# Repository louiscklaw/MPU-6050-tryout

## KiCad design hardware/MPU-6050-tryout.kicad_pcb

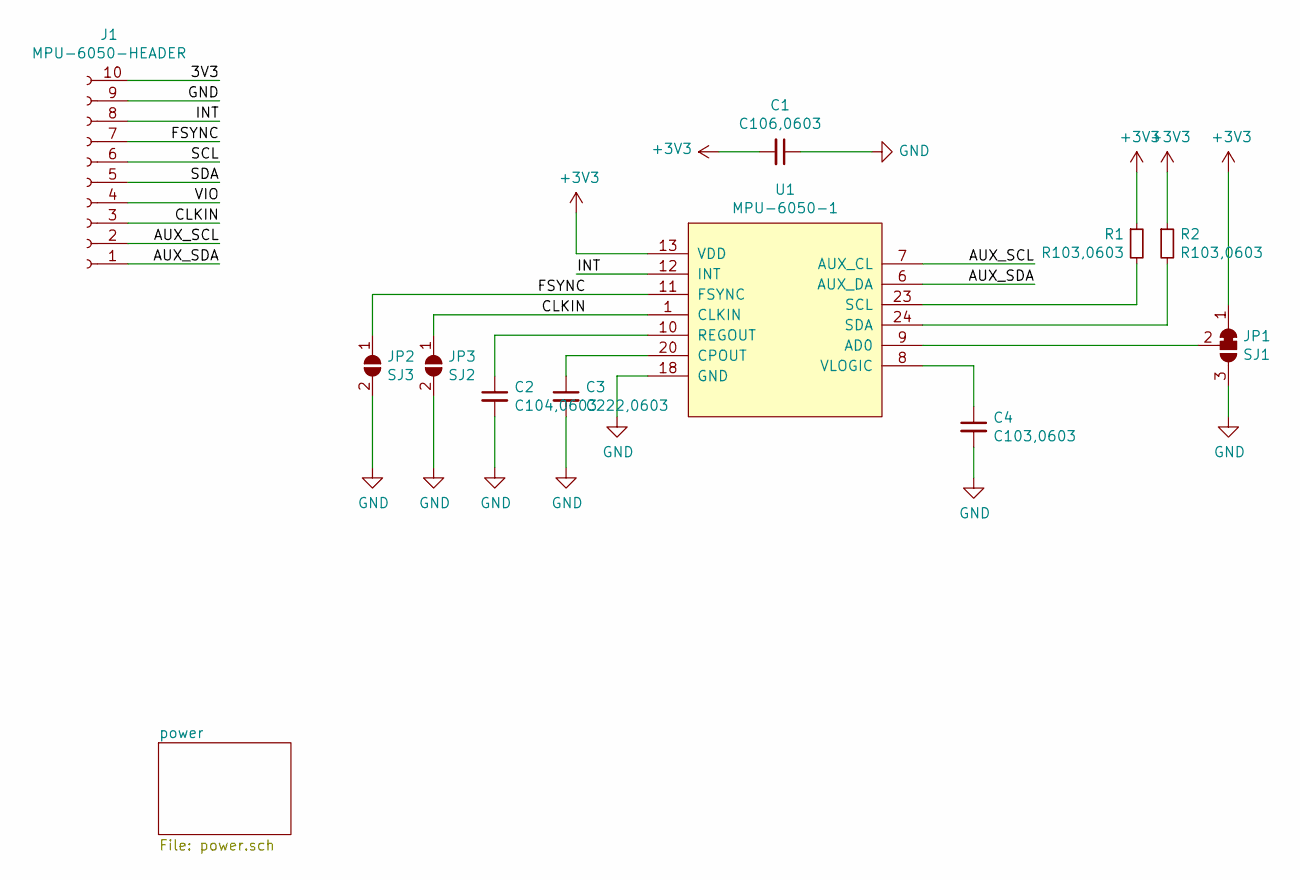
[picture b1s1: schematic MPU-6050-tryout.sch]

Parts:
C1: C106,0603; C_0603_1608Metric_Pad1.05x0.95mm_HandSolder
C2: C104,0603; C_0603_1608Metric_Pad1.05x0.95mm_HandSolder
C3: C222,0603; C_0603_1608Metric_Pad1.05x0.95mm_HandSolder
C4: C103,0603; C_0603_1608Metric_Pad1.05x0.95mm_HandSolder
J1: MPU-6050-HEADER; PinHeader_1x10_P1.27mm_Vertical
JP1: SJ1; SolderJumper-3_P1.3mm_Bridged2Bar12_Pad1.0x1.5mm
JP2: SJ3; SolderJumper-2_P1.3mm_Open_RoundedPad1.0x1.5mm
JP3: SJ2; SolderJumper-2_P1.3mm_Open_RoundedPad1.0x1.5mm
R1, R2: R103,0603; R_0603_1608Metric_Pad1.05x0.95mm_HandSolder
U1: MPU-6050-1; MPU-6050-QFN24

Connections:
+3V3: C1.2, JP1.1 (A), R1.1, R2.1, U1.13 (VDD); also elsewhere on the board
/3V3: J1.10
/AUX_SCL: J1.2, U1.7 (AUX_CL)
/AUX_SDA: J1.1, U1.6 (AUX_DA)
/CLKIN: J1.3, JP3.1 (A), U1.1 (CLKIN)
/FSYNC: J1.7, JP2.1 (A), U1.11 (FSYNC)
/INT: J1.8, U1.12 (INT)
/SCL: J1.6
/SDA: J1.5
/VIO: J1.4
GND: C1.1, C2.2, C3.2, C4.2, J1.9, JP1.3 (B), JP2.2 (B), JP3.2 (B), U1.18 (GND); also elsewhere on the board
unnamed: C2.1, U1.10 (REGOUT)
unnamed: C3.1, U1.20 (CPOUT)
unnamed: C4.1, U1.8 (VLOGIC)
unnamed: JP1.2 (C), U1.9 (AD0)
unnamed: R1.2, U1.23 (SCL)
unnamed: R2.2, U1.24 (SDA)

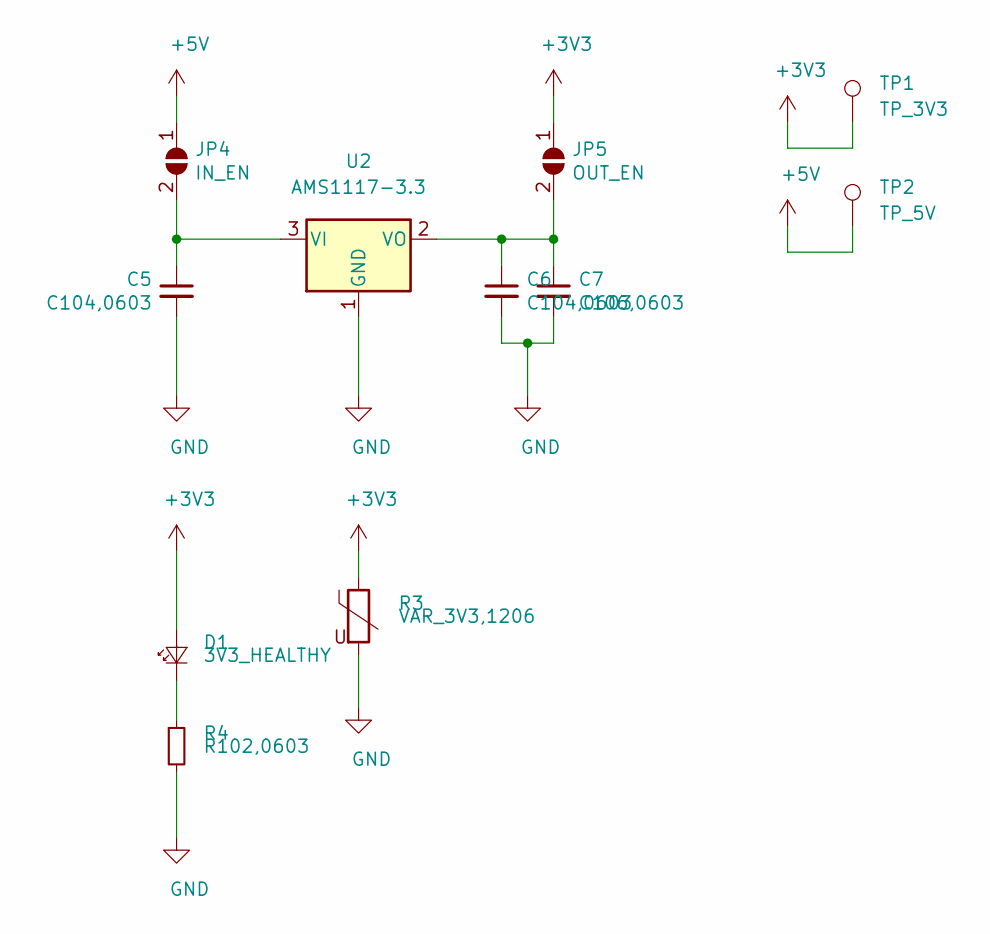
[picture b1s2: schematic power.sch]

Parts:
C5, C6: C104,0603; C_0603_1608Metric_Pad1.05x0.95mm_HandSolder
C7: C106,0603; C_0603_1608Metric_Pad1.05x0.95mm_HandSolder
D1: 3V3_HEALTHY; LED_0603_1608Metric_Pad1.05x0.95mm_HandSolder
JP4: IN_EN; SolderJumper-2_P1.3mm_Open_RoundedPad1.0x1.5mm
JP5: OUT_EN; SolderJumper-2_P1.3mm_Open_RoundedPad1.0x1.5mm
R3: VAR_3V3,1206; VAR_1206
R4: R102,0603; R_0603_1608Metric_Pad1.05x0.95mm_HandSolder
TP1: TP_3V3; Pin_D1.0mm_L10.0mm
TP2: TP_5V; Pin_D1.0mm_L10.0mm
U2: AMS1117-3.3; SOT-223-3_TabPin2

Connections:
+3V3: D1.2 (A), JP5.1 (A), R3.1, TP1.1; also elsewhere on the board
+5V: JP4.1 (A), TP2.1
GND: C5.2, C6.2, C7.2, R3.2, R4.2, U2.1 (GND); also elsewhere on the board
unnamed: C5.1, JP4.2 (B), U2.3 (VI)
unnamed: C6.1, C7.1, JP5.2 (B), U2.2 (VO)
unnamed: D1.1 (K), R4.1

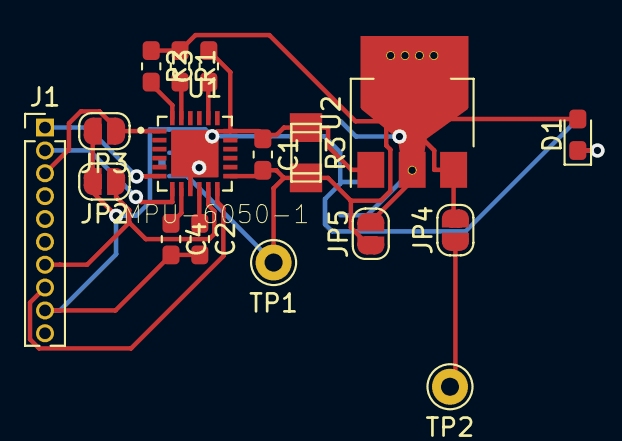
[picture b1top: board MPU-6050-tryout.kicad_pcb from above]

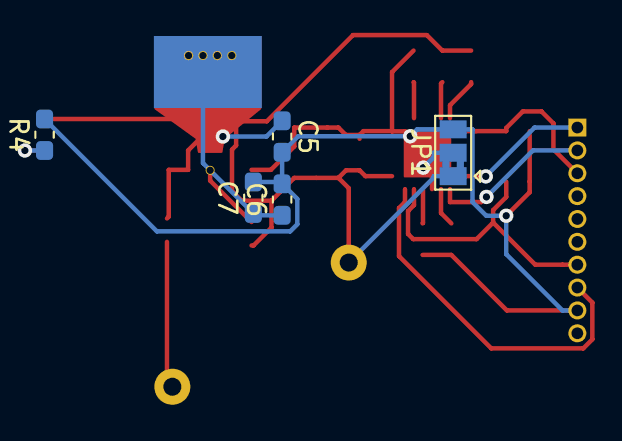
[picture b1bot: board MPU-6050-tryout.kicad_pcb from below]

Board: 2 copper layers, 22 parts (5 on the bottom side), 17 nets.

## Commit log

2019-06-26 update,
2020-05-06 ci: init travis token,
2020-05-06 ci: init travis build config,
